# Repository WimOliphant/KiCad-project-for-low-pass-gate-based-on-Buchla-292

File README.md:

# KiCad-project-for-low-pass-gate-based-on-Buchla-292

UNTESTED AND UNVERIFIED.

KiCad project files for circuit, PCB layout and PCB gerbers .zip.

Based on the schematic posted by Eddy Bergman: https://www.eddybergman.com/2020/10/synthesizer-build-part-35-resonant.html

In turn based on Buchla 292.

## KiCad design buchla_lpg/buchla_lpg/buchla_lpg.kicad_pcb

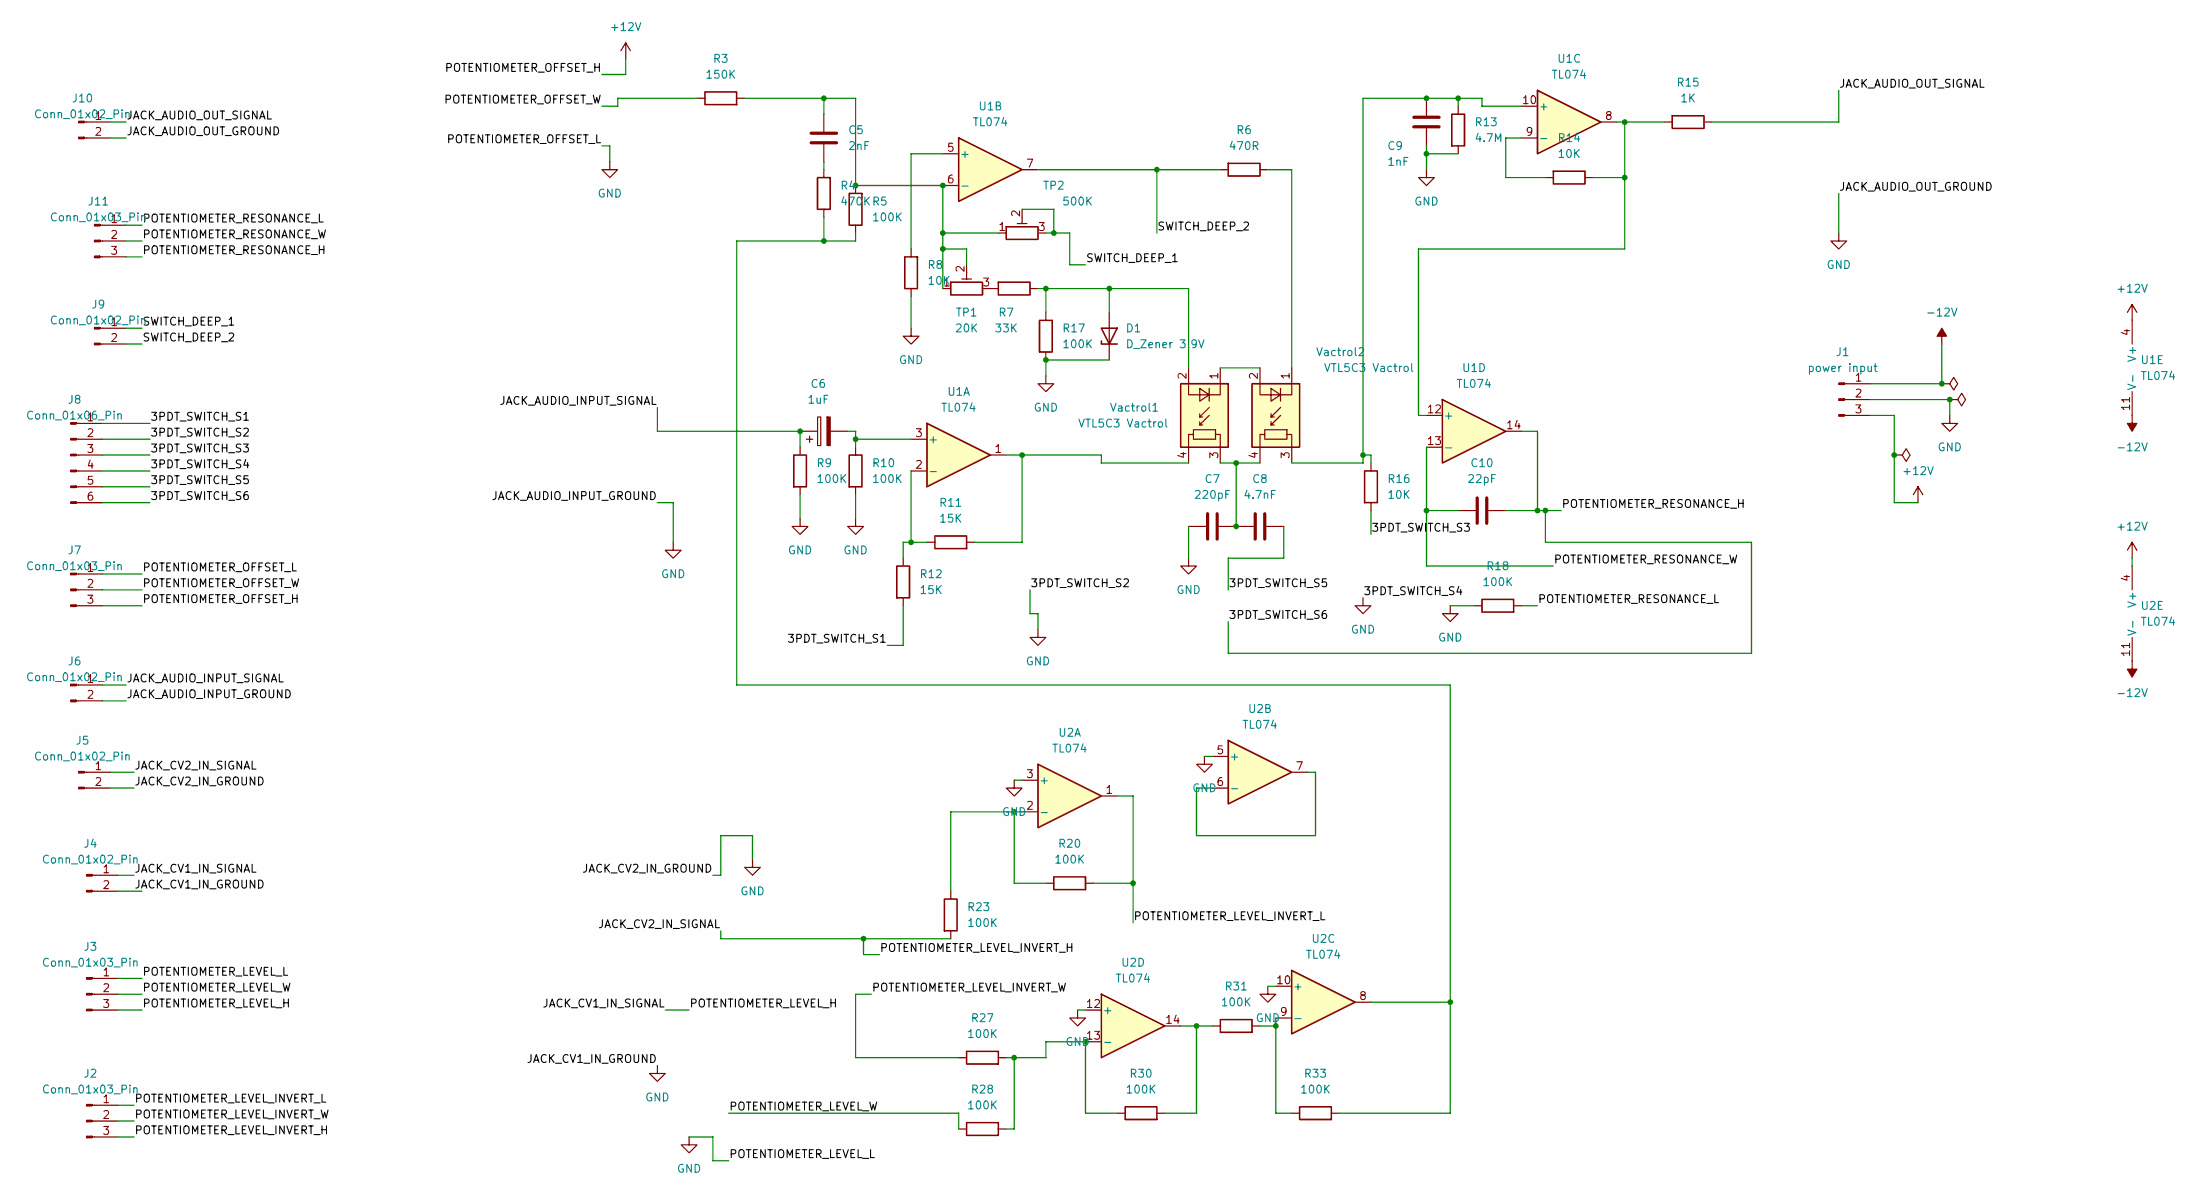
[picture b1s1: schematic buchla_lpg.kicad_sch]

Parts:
C5: 2nF; C_Disc_D5.0mm_W2.5mm_P5.00mm
C6: 1uF; CP_Radial_D6.3mm_P2.50mm
C7: 220pF; C_Disc_D5.0mm_W2.5mm_P5.00mm
C8: 4.7nF; C_Disc_D5.0mm_W2.5mm_P5.00mm
C9: 1nF; C_Disc_D5.0mm_W2.5mm_P5.00mm
C10: 22pF; C_Disc_D5.0mm_W2.5mm_P5.00mm
D1: D_Zener 3.9V; D_A-405_P10.16mm_Horizontal
J1: power input; Samtec_HPM-03-01-x-S_Straight_1x03_Pitch5.08mm
J2, J3, J7, J11: Conn_01x03_Pin; PinHeader_1x03_P2.54mm_Vertical
J4, J5, J6, J9, J10: Conn_01x02_Pin; PinHeader_1x02_P2.54mm_Vertical
J8: Conn_01x06_Pin; PinHeader_1x06_P2.54mm_Vertical
R3: 150K; R_Axial_DIN0204_L3.6mm_D1.6mm_P7.62mm_Horizontal
R4: 470K; R_Axial_DIN0204_L3.6mm_D1.6mm_P7.62mm_Horizontal
R5, R9, R10, R17, R18, R20, R23, R27, R28, R30, R31, R33: 100K; R_Axial_DIN0204_L3.6mm_D1.6mm_P7.62mm_Horizontal
R6: 470R; R_Axial_DIN0204_L3.6mm_D1.6mm_P7.62mm_Horizontal
R7: 33K; R_Axial_DIN0204_L3.6mm_D1.6mm_P7.62mm_Horizontal
R8, R14, R16: 10K; R_Axial_DIN0204_L3.6mm_D1.6mm_P7.62mm_Horizontal
R11, R12: 15K; R_Axial_DIN0204_L3.6mm_D1.6mm_P7.62mm_Horizontal
R13: 4.7M; R_Axial_DIN0204_L3.6mm_D1.6mm_P7.62mm_Horizontal
R15: 1K; R_Axial_DIN0204_L3.6mm_D1.6mm_P7.62mm_Horizontal
TP1: 20K; Potentiometer_Bourns_3266Y_Vertical
TP2: 500K; Potentiometer_Bourns_3266Y_Vertical
U1, U2: TL074; DIP-14_W7.62mm_LongPads
Vactrol1, Vactrol2: VTL5C3 Vactrol; PerkinElmer_VTL5C

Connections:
+12V: J1.3, J7.3, U1.4 (V+), U2.4 (V+)
-12V: J1.1, U1.11 (V-), U2.11 (V-)
/3PDT_SWITCH_S1: J8.1, R12.2
/3PDT_SWITCH_S3: J8.3, R16.2
/3PDT_SWITCH_S5: C8.2, J8.5
/3PDT_SWITCH_S6: C10.2, J8.6, J11.3, U1.14
/JACK_AUDIO_INPUT_SIGNAL: C6.1, J6.1, R9.1
/JACK_AUDIO_OUT_SIGNAL: J10.1, R15.1
/JACK_CV1_IN_SIGNAL: J3.3, J4.1
/JACK_CV2_IN_SIGNAL: J2.3, J5.1, R23.2
/POTENTIOMETER_LEVEL_INVERT_L: J2.1, R20.2, U2.1
/POTENTIOMETER_LEVEL_INVERT_W: J2.2, R27.1
/POTENTIOMETER_LEVEL_W: J3.2, R28.1
/POTENTIOMETER_OFFSET_W: J7.2, R3.1
/POTENTIOMETER_RESONANCE_L: J11.1, R18.2
/POTENTIOMETER_RESONANCE_W: C10.1, J11.2, U1.13 (-)
/SWITCH_DEEP_1: J9.1, TP2.2, TP2.3
/SWITCH_DEEP_2: J9.2, R6.2, U1.7
GND: C7.1, C9.2, D1.1 (K), J1.2, J3.1, J4.2, J5.2, J6.2, J7.1, J8.2, J8.4, J10.2, R8.1, R9.2, R10.2, R13.2, R17.2, R18.1, U2.3 (+), U2.5 (+), U2.10 (+), U2.12 (+)
unnamed: C5.2, R4.2
unnamed: C7.2, C8.1, Vactrol1.3, Vactrol2.4
unnamed: D1.2 (A), R7.1, R17.1, Vactrol1.2 (+)
unnamed: R7.2, TP1.3
unnamed: R11.2, U1.1, Vactrol1.4
unnamed: R30.2, R31.1, U2.14
unnamed: R4.1, R5.1, R33.2, U2.8
unnamed: C6.2, R10.1, U1.3 (+)
unnamed: R11.1, R12.1, U1.2 (-)
unnamed: R8.2, U1.5 (+)
unnamed: C5.1, R3.2, R5.2, TP1.1, TP1.2, TP2.1, U1.6 (-)
unnamed: C9.1, R13.1, R16.1, U1.10 (+), Vactrol2.3
unnamed: R14.2, U1.9 (-)
unnamed: R14.1, R15.2, U1.8, U1.12 (+)
unnamed: R20.1, R23.1, U2.2 (-)
unnamed: U2.6 (-), U2.7
unnamed: R31.2, R33.1, U2.9 (-)
unnamed: R27.2, R28.2, R30.1, U2.13 (-)
unnamed: Vactrol1.1 (-), Vactrol2.2 (+)
unnamed: R6.1, Vactrol2.1 (-)

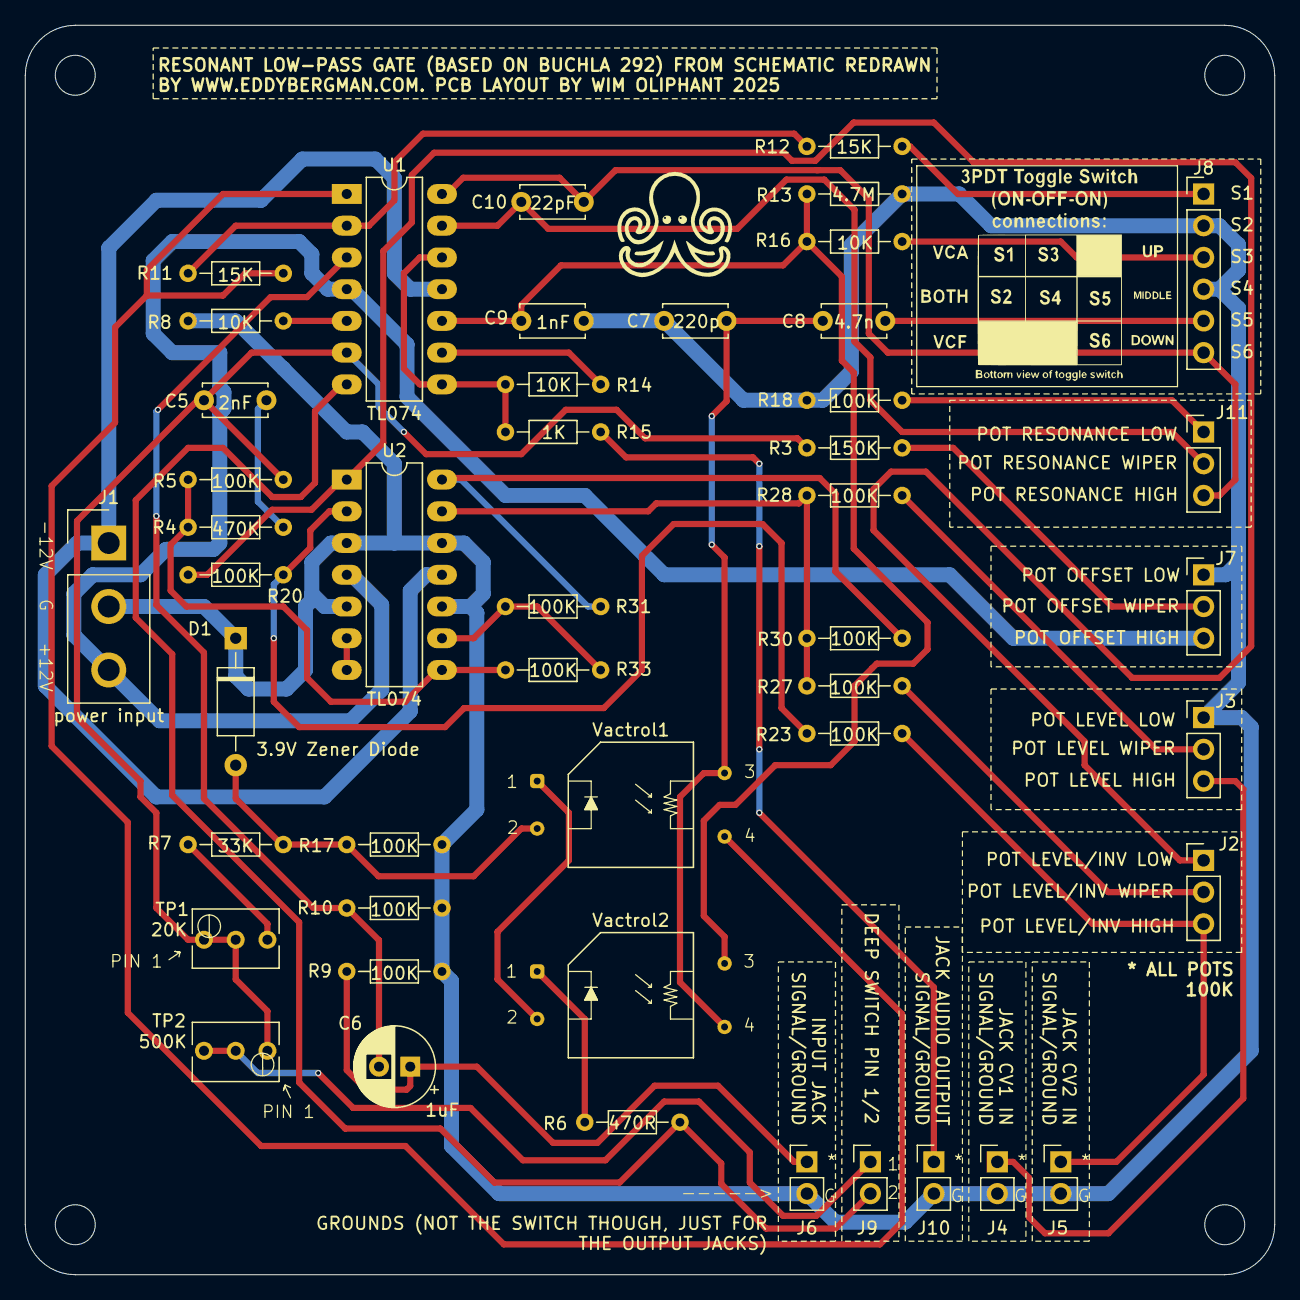
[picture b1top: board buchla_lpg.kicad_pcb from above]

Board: 2 copper layers, 100.0 x 100.0 mm, 47 parts (0 on the bottom side), 39 nets.

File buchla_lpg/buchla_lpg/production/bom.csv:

Designator,Footprint,Quantity,Value,LCSC Part #
C10,C_Disc_D5.0mm_W2.5mm_P5.00mm,1,22pF,
C5,C_Disc_D5.0mm_W2.5mm_P5.00mm,1,2nF,
C6,CP_Radial_D6.3mm_P2.50mm,1,1uF,
C7,C_Disc_D5.0mm_W2.5mm_P5.00mm,1,220p,
C8,C_Disc_D5.0mm_W2.5mm_P5.00mm,1,4.7n,
C9,C_Disc_D5.0mm_W2.5mm_P5.00mm,1,1nF,
D1,D_A-405_P10.16mm_Horizontal,1,3.9V Zener Diode,
J1,Samtec_HPM-03-01-x-S_Straight_1x03_Pitch5.08mm,1,power input,
"J10, J4, J5, J6, J9",PinHeader_1x02_P2.54mm_Vertical,5,Conn_01x02_Pin,
"J11, J2, J3, J7",PinHeader_1x03_P2.54mm_Vertical,4,Conn_01x03_Pin,
J8,PinHeader_1x06_P2.54mm_Vertical,1,Conn_01x06_Pin,
"R10, R17, R18, R20, R23, R27, R28, R30, R31, R33, R5, R9",R_Axial_DIN0204_L3.6mm_D1.6mm_P7.62mm_Horizontal,12,100K,
"R11, R12",R_Axial_DIN0204_L3.6mm_D1.6mm_P7.62mm_Horizontal,2,15K,
R13,R_Axial_DIN0204_L3.6mm_D1.6mm_P7.62mm_Horizontal,1,4.7M,
"R14, R16, R8",R_Axial_DIN0204_L3.6mm_D1.6mm_P7.62mm_Horizontal,3,10K,
R15,R_Axial_DIN0204_L3.6mm_D1.6mm_P7.62mm_Horizontal,1,1K,
R3,R_Axial_DIN0204_L3.6mm_D1.6mm_P7.62mm_Horizontal,1,150K,
R4,R_Axial_DIN0204_L3.6mm_D1.6mm_P7.62mm_Horizontal,1,470K,
R6,R_Axial_DIN0204_L3.6mm_D1.6mm_P7.62mm_Horizontal,1,470R,
R7,R_Axial_DIN0204_L3.6mm_D1.6mm_P7.62mm_Horizontal,1,33K,
TP1,Potentiometer_Bourns_3266Y_Vertical,1,20K,
TP2,Potentiometer_Bourns_3266Y_Vertical,1,500K,
"U1, U2",DIP-14_W7.62mm_LongPads,2,TL074,
"VACTROL1, VACTROL2",PerkinElmer_VTL5C,2,VTL5C3 Vactrol,
